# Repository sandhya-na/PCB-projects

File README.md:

# PCB Design Portfolio
This repository contains my original hardware designs developed in KiCad 10. These projects focus on power regulation and PCB layout best practices, including thermal management and signal integrity.

## 1. 12V AC to 5V DC Linear Power Supply
   This project is a regulated power supply designed to convert 12V AC input into a stable 5V DC output.
   ## Technical Design Details
      * Rectification Stage: 
            Uses a full-bridge rectifier consisting of four 1N4007 diodes to convert the AC input to pulsating DC.
      * Regulation:
            Features an LM7805 linear regulator in a TO-220 package to provide a constant 5V output.
      * Filtering System:
         - A large 1000µF electrolytic capacitor (C1) is used for bulk smoothing of the rectified AC ripple.
         -  0.1µF ceramic capacitors (C2, C3) are placed close to the regulator pins to filter out high-frequency noise.
      * Circuit Protection:
            Includes an input fuse (F1) to protect the components from overcurrent or short-circuit conditions.                   
      * Visual Indication:
            An on-board LED with a 2.2kΩ resistor provides immediate status of the output power.
   ## PCB Layout Strategy
   The layout focuses on safety and stability. I prioritized proper spacing between the AC input terminals and the DC output to prevent interference and ensured the LM7805 has enough space for heat dissipation.
## 2. Adjustable DC-DC Buck Converter
   This project is a high-efficiency switching regulator based on the LM2596-ADJ IC, used for stepping down DC voltages.
   ## Technical Design Details
    *  Switching Regulator:
           Powered by the LM2596S-ADJ, which operates at a switching frequency of 150kHz for high efficiency.
    * Adjustable Output:
          Uses a 10kΩ potentiometer (RV1) in the feedback loop, allowing the user to precisely set the desired output voltage.
    * Power Components :
       - A 47µH inductor (L1) and a Schottky diode (D2) are used for energy storage and current steering during the switching cycle.         -  Features a 100µF input cap and a 220µF output cap to stabilize the switching waveforms.
    * Indication:
          Includes a power-on LED with a 4.7kΩ resistor.
## PCB Layout Strategy
For this layout, I focused on Power Integrity:
  * **Wide Copper Pours**: I used large copper areas for the VIN and VOUT nets to handle higher currents without overheating the traces.
  * **Switching Loop** : I placed the diode, inductor, and IC as close together as possible to minimize the loop area, which helps reduce EMI (Electro-Magnetic Interference).
  * **Ground Plane**: A solid ground reference was used to ensure low-noise operation of the feedback pin.

# Tools & Methodology
## * Software: KiCad 10.0
## * Process : Schematic Capture → Footprint Assignment → PCB Routing → 3D Visualization → PDF Documentation.

Contact: sandhyana384@gmail.com

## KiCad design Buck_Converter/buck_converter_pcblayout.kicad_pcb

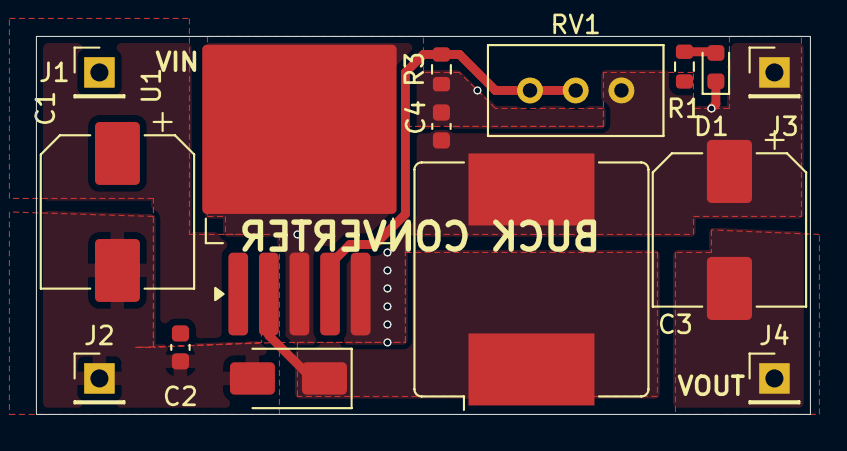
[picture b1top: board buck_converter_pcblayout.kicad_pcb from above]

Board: 2 copper layers, 43.0 x 21.0 mm, 15 parts (0 on the bottom side), 6 nets.

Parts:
C1: 100uF; CP_Elec_8x10
C2, C4: 100nF; C_0603_1608Metric
C3: 220uF; CP_Elec_8x10
D1: LED; LED_0603_1608Metric
D2: SS34; D_SMA
J1, J2, J3, J4: PinHeader_1x01_P2.54mm_Vertical
L1: 47uH; L_Bourns_SRR1208_12.7x12.7mm
R1: 4K7; R_0603_1608Metric
R3: 1K; R_0603_1608Metric
RV1: 10K; Potentiometer_Bourns_3296W_Vertical
U1: TO-263-5_TabPin3

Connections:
GND: C1.2, C2.2, C3.2, C4.2, D1.1 (K), D2.2 (A), J2.1 (Pin_1_1), J4.1 (Pin_1_1), R3.2, U1.3 (GND), U1.5 (~ON/OFF)
unnamed: D1.2 (A), R1.2
unnamed: D2.1 (K), L1.1, U1.2 (OUT)
unnamed: C1.1, C2.1, J1.1 (Pin_1_1), U1.1 (VIN)
unnamed: C3.1, C4.1, J3.1 (Pin_1_1), L1.2, R1.1, RV1.1
unnamed: R3.1, RV1.2, RV1.3, U1.4 (FB)

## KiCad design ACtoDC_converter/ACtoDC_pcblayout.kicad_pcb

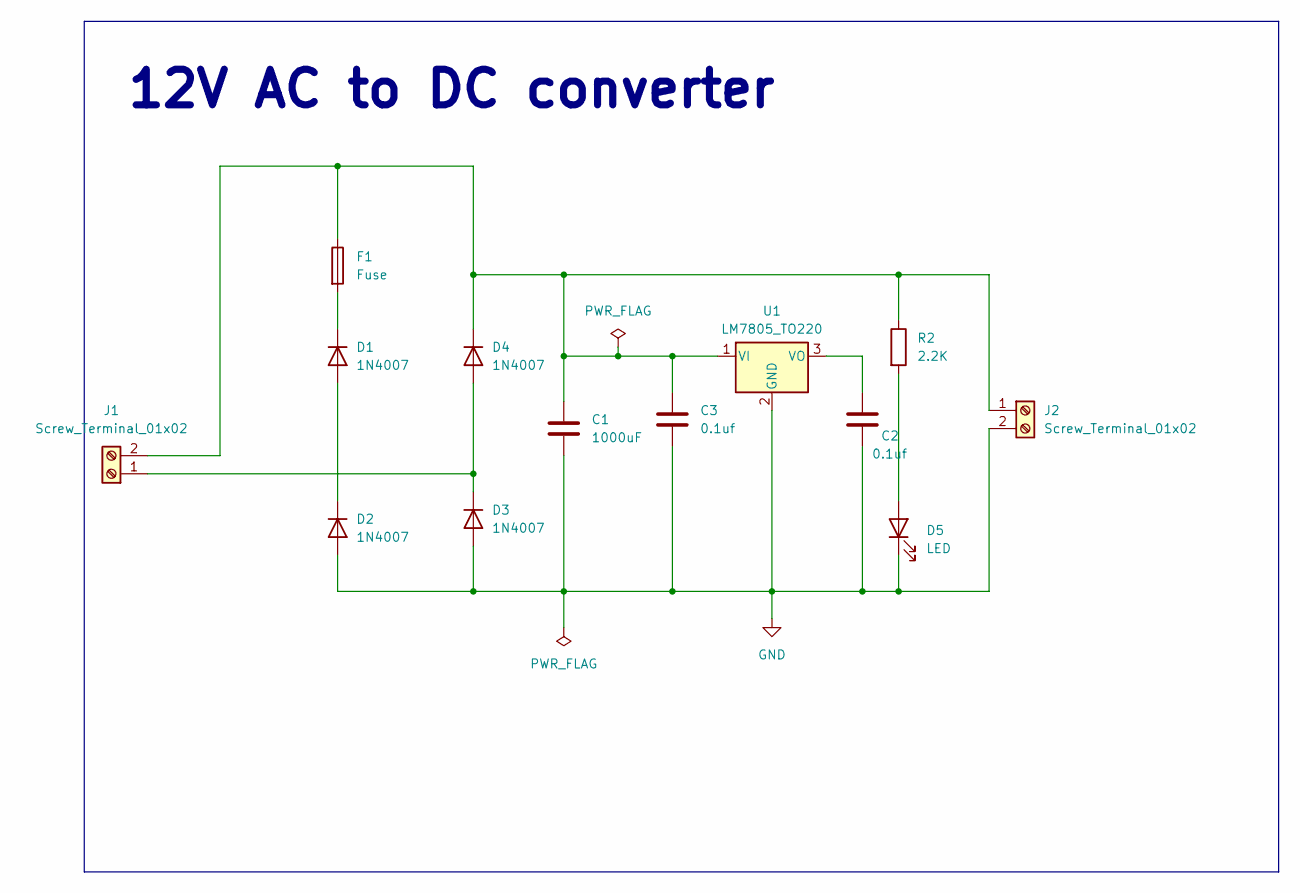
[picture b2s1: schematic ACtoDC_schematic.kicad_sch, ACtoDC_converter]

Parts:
C1: 1000uF; C_Radial_D8.0mm_H11.5mm_P3.50mm
C2, C3: 0.1uf; CP_Radial_D10.0mm_P5.00mm
D1, D2, D3, D4: 1N4007; D_DO-41_SOD81_P10.16mm_Horizontal
D5: LED; LED_D5.0mm
F1: Fuse; Fuseholder_Cylinder-5x20mm_Schurter_0031_8201_Horizontal_Op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
J1, J2: Screw_Terminal_01x02; TerminalBlock_MaiXu_MX126-5.0-02P_1x02_P5.00mm
R2: 2.2K; R_Axial_DIN0204_L3.6mm_D1.6mm_P7.62mm_Horizontal
U1: LM7805_TO220; TO-220-3_Vertical

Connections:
GND: C1.2, C2.2, C3.2, D2.2 (A), D3.2 (A), D5.1 (K), J2.2, U1.2 (GND)
unnamed: D1.2 (A), D2.1 (K)
unnamed: D1.1 (K), F1.2
unnamed: D3.1 (K), D4.2 (A), J1.1
unnamed 4: C1.1, C3.1, D4.1 (K), F1.1, J1.2, J2.1, R2.1, U1.1 (VI); also elsewhere on the board
unnamed 5: D5.2 (A), R2.2; also elsewhere on the board
unnamed: C2.1, U1.3 (VO)

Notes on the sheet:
12V AC to DC converter

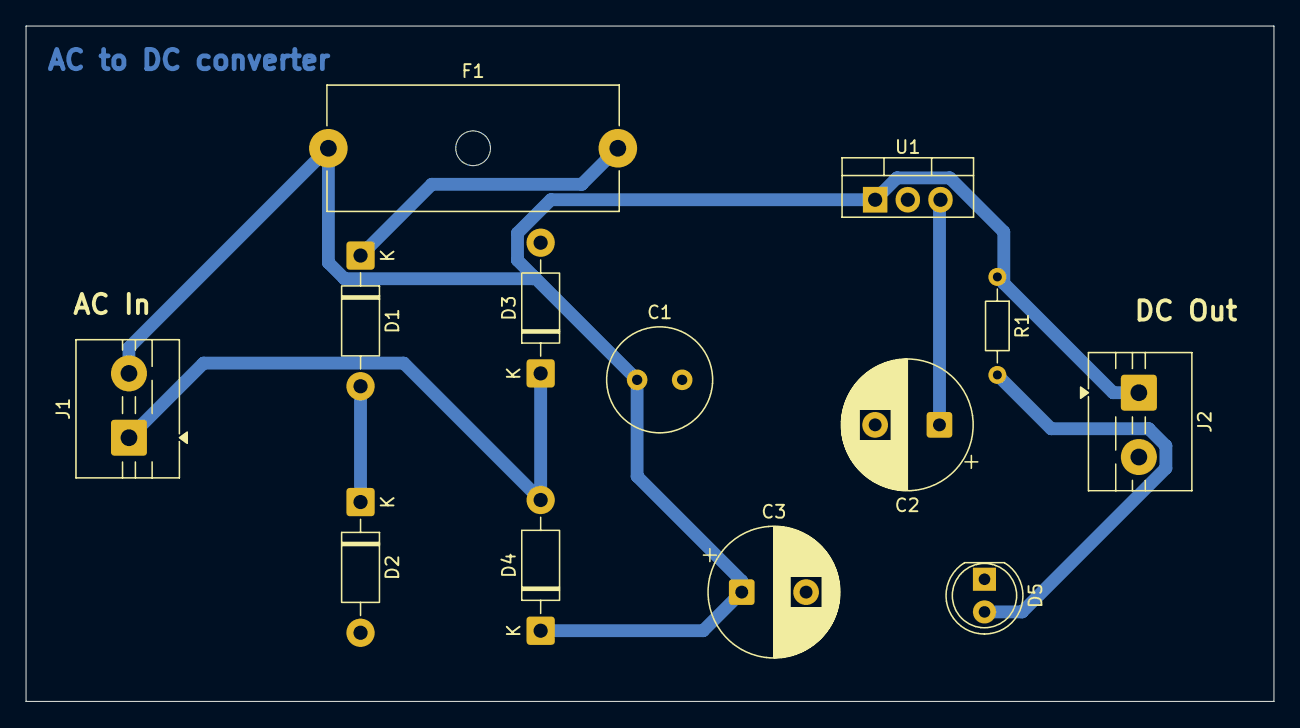
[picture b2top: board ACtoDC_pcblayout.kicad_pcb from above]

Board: 2 copper layers, 97.0 x 52.5 mm, 13 parts (0 on the bottom side), 7 nets.

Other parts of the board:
R1: 2.2K; R_Axial_DIN0204_L3.6mm_D1.6mm_P7.62mm_Horizontal

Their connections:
unnamed 4: R1.1; also elsewhere on the board
unnamed 5: R1.2; also elsewhere on the board

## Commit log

2026-04-20 Create temp
2026-04-20 Added schematic, layout, and 3Dview
2026-04-20 added pdf files
2026-04-20 Create Buck_Converter
2026-04-20 Added schematic, Layout, 3D view and pdf files
